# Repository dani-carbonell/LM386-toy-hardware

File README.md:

# LM386-toy-hardware
Kicad project - LM386 for DIY sound toys

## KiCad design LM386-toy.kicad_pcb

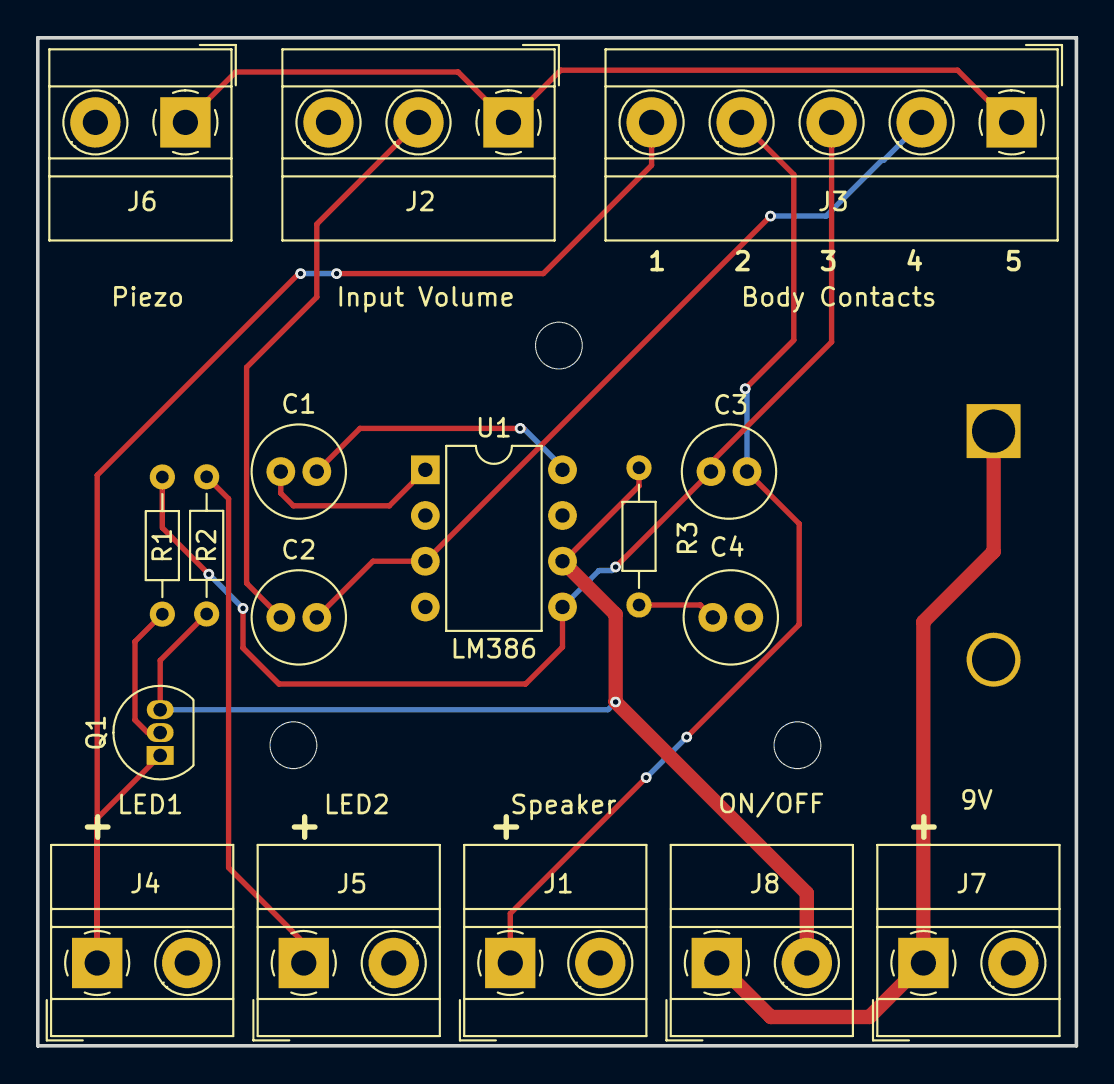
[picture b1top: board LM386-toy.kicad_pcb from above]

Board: 2 copper layers, 57.7 x 56.0 mm, 18 parts (1 on the bottom side), 14 nets.

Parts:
BT1: Battery; BatteryHolder_Eagle_12BH611-GR
C1: 10uF; C_Radial_D5.0mm_H11.0mm_P2.00mm
C2: C_Polarized; C_Radial_D5.0mm_H11.0mm_P2.00mm
C3: 100uF; C_Radial_D5.0mm_H11.0mm_P2.00mm
C4: 1uF; C_Radial_D5.0mm_H11.0mm_P2.00mm
J1: Speaker; TerminalBlock_MetzConnect_Type011_RT05502HBWC_1x02_P5.00mm_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
J2: Input Volume; TerminalBlock_MetzConnect_Type011_RT05503HBWC_1x03_P5.00mm_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
J3: Body Contacts; TerminalBlock_MetzConnect_Type011_RT05505HBWC_1x05_P5.00mm_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
J4: LED1; TerminalBlock_MetzConnect_Type011_RT05502HBWC_1x02_P5.00mm_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
J5: LED2; TerminalBlock_MetzConnect_Type011_RT05502HBWC_1x02_P5.00mm_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
J6: Piezo; TerminalBlock_MetzConnect_Type011_RT05502HBWC_1x02_P5.00mm_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
J7: 9V; TerminalBlock_MetzConnect_Type011_RT05502HBWC_1x02_P5.00mm_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
J8: ON/OFF; TerminalBlock_MetzConnect_Type011_RT05502HBWC_1x02_P5.00mm_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
Q1: 2N3904; TO-92_Inline
R1, R2, R3: R; R_Axial_DIN0204_L3.6mm_D1.6mm_P7.62mm_Horizontal
U1: LM386; DIP-8_W7.62mm

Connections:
+9V: BT1.1 (+), J7.1, J8.1
/led1+: J3.5, J4.1, Q1.1 (E)
/led2+: J5.1, R1.2
/piezo+: J2.1, J3.1, J6.1
/signal_in: C2.1, J2.2
/spk+: C3.2, J1.1, J3.4
/touch2: C2.2, J3.2, U1.3 (+)
/touch3: C3.1, J3.3, R2.1, U1.5
GND: BT1.2 (-), C4.2, J1.2, J2.3, J4.2, J5.2, J6.2, J7.2, U1.2 (-), U1.4 (GND)
unnamed: C1.1, U1.1 (GAIN)
unnamed: C1.2, U1.8 (GAIN)
unnamed: C4.1, R3.2
unnamed: Q1.2 (B), R2.2
VCC: J8.2, Q1.3 (C), R1.1, R3.1, U1.6 (V+)

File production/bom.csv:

Designator,Footprint,Quantity,Value,LCSC Part #
BT1,BatteryHolder_Eagle_12BH611-GR,1,Battery,
C1,C_Radial_D5.0mm_H11.0mm_P2.00mm,1,10uF,
C2,C_Radial_D5.0mm_H11.0mm_P2.00mm,1,C_Polarized,
C3,C_Radial_D5.0mm_H11.0mm_P2.00mm,1,100uF,
C4,C_Radial_D5.0mm_H11.0mm_P2.00mm,1,1uF,
J1,TerminalBlock_MetzConnect_Type011_RT05502HBWC_1x02_P5.00mm_Horizontal,1,Speaker,
J2,TerminalBlock_MetzConnect_Type011_RT05503HBWC_1x03_P5.00mm_Horizontal,1,Input Volume,
J3,TerminalBlock_MetzConnect_Type011_RT05505HBWC_1x05_P5.00mm_Horizontal,1,Body Contacts,
J4,TerminalBlock_MetzConnect_Type011_RT05502HBWC_1x02_P5.00mm_Horizontal,1,LED1,
J5,TerminalBlock_MetzConnect_Type011_RT05502HBWC_1x02_P5.00mm_Horizontal,1,LED2,
J6,TerminalBlock_MetzConnect_Type011_RT05502HBWC_1x02_P5.00mm_Horizontal,1,Piezo,
J7,TerminalBlock_MetzConnect_Type011_RT05502HBWC_1x02_P5.00mm_Horizontal,1,9V,
J8,TerminalBlock_MetzConnect_Type011_RT05502HBWC_1x02_P5.00mm_Horizontal,1,ON/OFF,
Q1,TO-92_Inline,1,2N3904,
"R1, R2, R3",R_Axial_DIN0204_L3.6mm_D1.6mm_P7.62mm_Horizontal,3,R,
U1,DIP-8_W7.62mm,1,LM386,

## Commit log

2024-08-24 add kicad files
2024-08-27 fabrication v1
2025-03-12 Update project structure: add .gitignore, remove LICENSE, and introduce interactive BOM HTML file. Update KiCad project files with new settings and remove old backups.
2025-03-12 Remove lock file and footprint info cache from the project.
